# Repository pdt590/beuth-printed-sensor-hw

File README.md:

# PrintED

Readout device hardware for PrintED project

- Readout Device

Front                              |  Edge
:---------------------------------:|:--------------------------------------:
  | 

- Readout Device with PrintED Sensor

- System Deployment

## Compatibility

- [beuth-printed-sensor-fw](https://github.com/pdt590/beuth-printed-sensor-fw)
- [beuth-printed-app](https://github.com/pdt590/beuth-printed-app)
- [beuth-printed-cloud](https://github.com/pdt590/beuth-printed-cloud)

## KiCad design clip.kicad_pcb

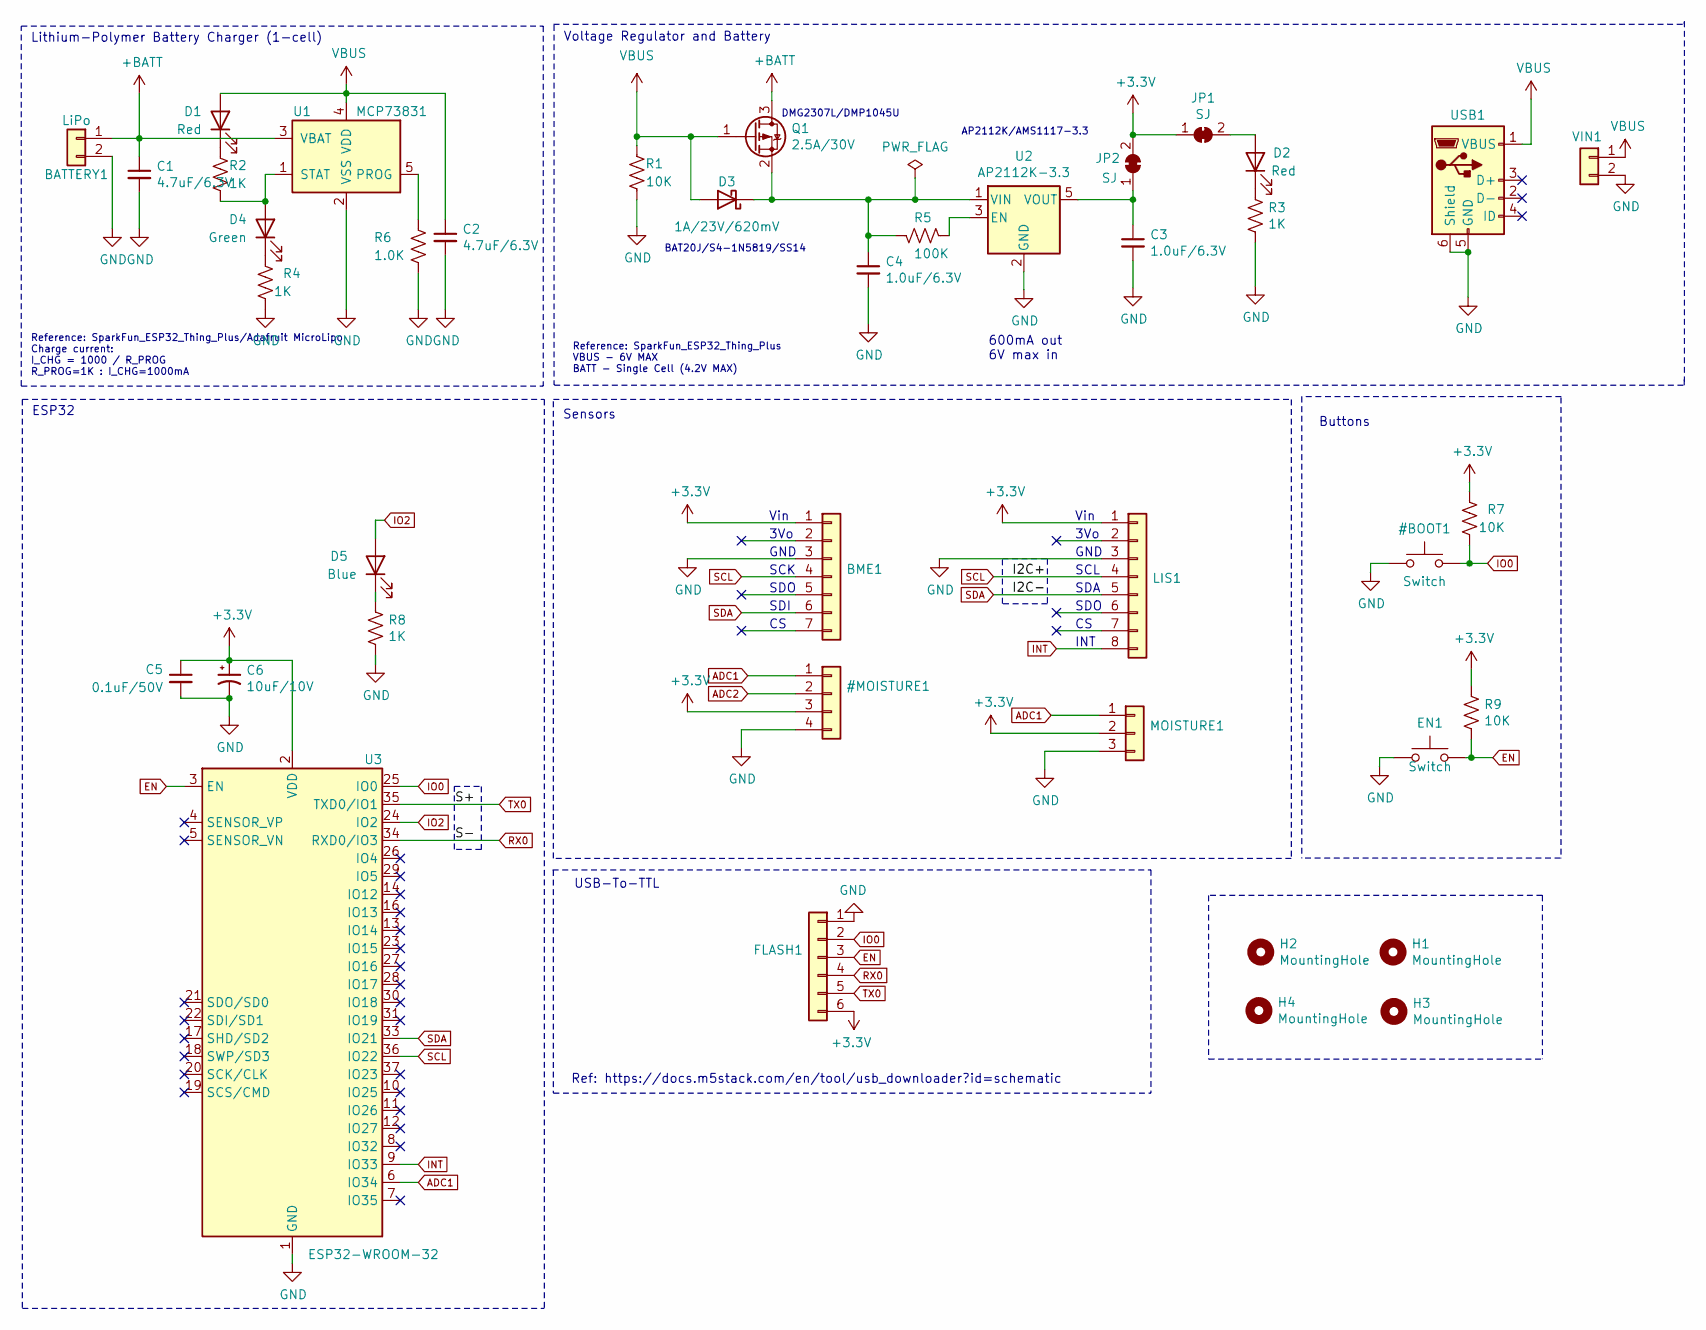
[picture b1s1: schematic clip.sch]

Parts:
BATTERY1: LiPo; JST_PH_S2B-PH-K_1x02_P2.00mm_Horizontal; Digikey 455-1719-ND
BME1: BME680; PinHeader_1x07_P2.54mm_Vertical; Digikey S7006-ND
C1, C2: 4.7uF/6.3V; C_0805_2012Metric_Pad1.15x1.40mm_HandSolder; Digikey 732-7647-1-ND
C3, C4: 1.0uF/6.3V; C_0805_2012Metric_Pad1.15x1.40mm_HandSolder; Digikey 732-7654-1-ND
C5: 0.1uF/50V; C_0805_2012Metric_Pad1.15x1.40mm_HandSolder; Digikey 732-8080-1-ND
C6: 10uF/10V; C_0805_2012Metric_Pad1.15x1.40mm_HandSolder; Digikey 478-3346-1-ND
D1: Red; LED_0805_2012Metric_Pad1.15x1.40mm_HandSolder; Digikey 732-4984-1-ND
D2: Red; LED_0805_2012Metric_Pad1.15x1.40mm_HandSolder; Digikey 732-4987-1-ND
D3: 1A/23V/620mV; D_SOD-323_HandSoldering; Digikey 497-3381-1-ND
D4: Green; LED_0805_2012Metric_Pad1.15x1.40mm_HandSolder; Digikey 732-4983-1-ND
D5: Blue; LED_0805_2012Metric_Pad1.15x1.40mm_HandSolder; Digikey 732-4982-1-ND
EN1: Switch; SW_SPST_B3U-1000P-B; Digikey SW1020CT-ND
FLASH1: Conn_01x07; PinHeader_1x06_P2.54mm_Vertical; Digikey 732-5323-ND
H1, H2, H3, H4: MountingHole; MountingHole_2.2mm_M2_DIN965_Pad
JP1, JP2: SJ; SolderJumper-2_P1.3mm_Open_TrianglePad1.0x1.5mm; Digikey 732-5328-ND
LIS1: LIS3DH; PinHeader_1x08_P2.54mm_Vertical; Digikey S7006-ND
MOISTURE1: MOISTURE; PinHeader_1x03_P2.54mm_Vertical
Q1: 2.5A/30V; SOT-23_Handsoldering; Digikey DMG2307L-7DICT-ND
R1, R7, R9: 10K; R_0805_2012Metric_Pad1.15x1.40mm_HandSolder; Digikey P10KDACT-ND
R2, R3, R4, R8: 1K; R_0805_2012Metric_Pad1.15x1.40mm_HandSolder; Digikey P1.0KDACT-ND
R5: 100K; R_0805_2012Metric_Pad1.15x1.40mm_HandSolder; Digikey P100KDACT-ND
R6: 1.0K; R_0805_2012Metric_Pad1.15x1.40mm_HandSolder; Digikey P2.0KDACT-ND
U1: MCP73831; SOT-23-5_HandSoldering; Digikey MCP73831T-2ACI/OTCT-ND
U2: AP2112K-3.3; SOT-23-5_HandSoldering; Digikey AP2112K-3.3TRG1DICT-ND
U3: ESP32-WROOM-32; Digikey 1904-1010-1-ND
USB1: USB_B_Micro; USB_Micro-B_Wuerth_629105150521; Digikey 732-5960-1-ND
VIN1: Conn_01x07; PinHeader_1x02_P2.54mm_Vertical; Digikey 732-5323-ND

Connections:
+BATT: BATTERY1.1, C1.1, Q1.3 (D), U1.3 (VBAT)
EN: EN1.2, FLASH1.3, R9.2, U3.3 (EN)
INT: LIS1.8, U3.9 (IO33)
IO2: D5.2 (A), U3.24 (IO2)
unnamed: C3.1, JP2.1 (A), U2.5 (VOUT)
unnamed: C4.1, D3.1 (K), Q1.2 (S), R5.2, U2.1 (VIN)
unnamed: D1.1 (K), R2.2
unnamed: D2.1 (K), R3.1
unnamed: D2.2 (A), JP1.2 (B)
unnamed: D4.1 (K), R4.2
unnamed: D4.2 (A), R2.1, U1.1 (STAT)
unnamed: D5.1 (K), R8.1
unnamed: R5.1, U2.3 (EN)
unnamed: R6.1, U1.5 (PROG)
RX0: FLASH1.4, U3.34 (RXD0/IO3)
SCL: BME1.4, LIS1.4, U3.36 (IO22)
SDA: BME1.6, LIS1.5, U3.33 (IO21)
TX0: FLASH1.5, U3.35 (TXD0/IO1)
VBUS: C2.1, D1.2 (A), D3.2 (A), Q1.1 (G), R1.2, U1.4 (VDD), USB1.1 (VBUS), VIN1.1

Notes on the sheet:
Voltage Regulator and Battery
Lithium-Polymer Battery Charger (1-cell)
ESP32
Buttons
Sensors
AP2112K/AMS1117-3.3
DMG2307L/DMP1045U
BAT20J/S4-1N5819/SS14
600mA out 6V max in
INT
SDO
SDA
SCL
GND
3Vo
Vin
SDI
SCK
GND
Reference: SparkFun_ESP32_Thing_Plus/Adafruit MicroLipo Charge current: I_CHG = 1000 / R_PROG R_PROG=1K : I_CHG=1000mA
Reference: SparkFun_ESP32_Thing_Plus VBUS - 6V MAX BATT - Single Cell (4.2V MAX)
Ref: https://docs.m5stack.com/en/tool/usb_downloader?id=schematic
USB-To-TTL

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
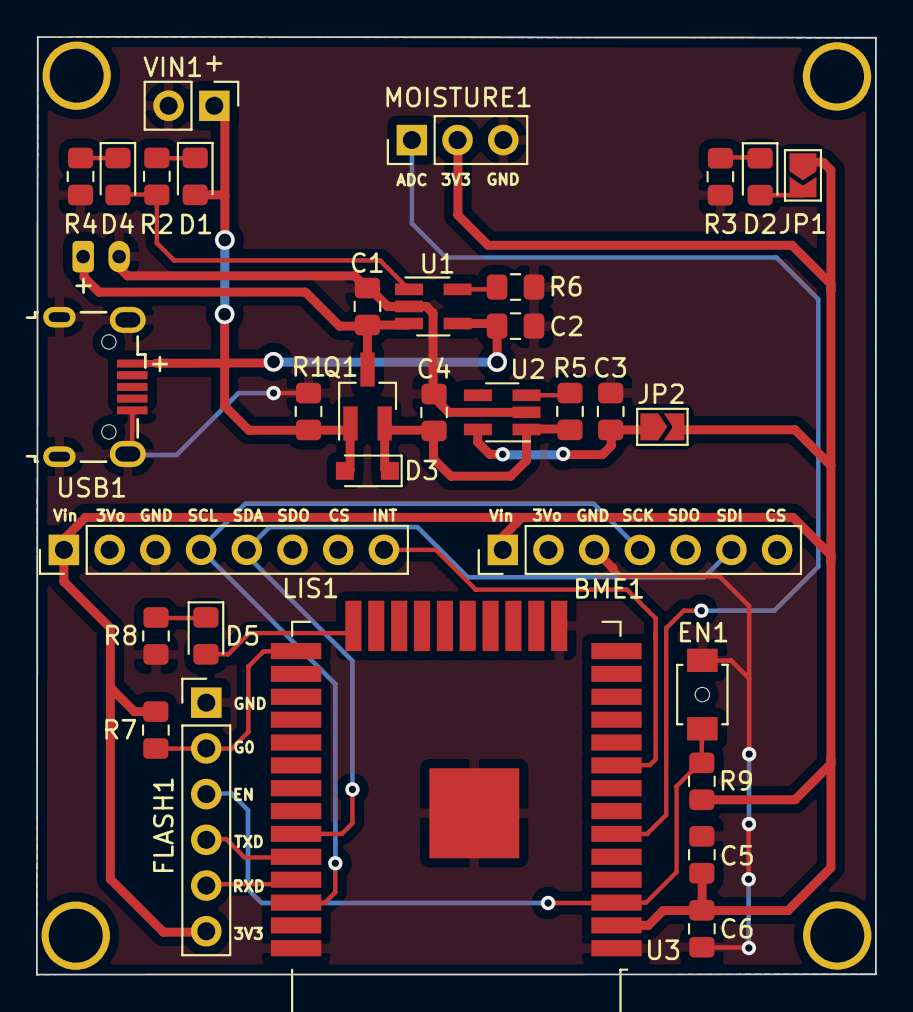
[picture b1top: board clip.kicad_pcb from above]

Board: 2 copper layers, 46.6 x 52.1 mm, 38 parts (1 on the bottom side), 23 nets.

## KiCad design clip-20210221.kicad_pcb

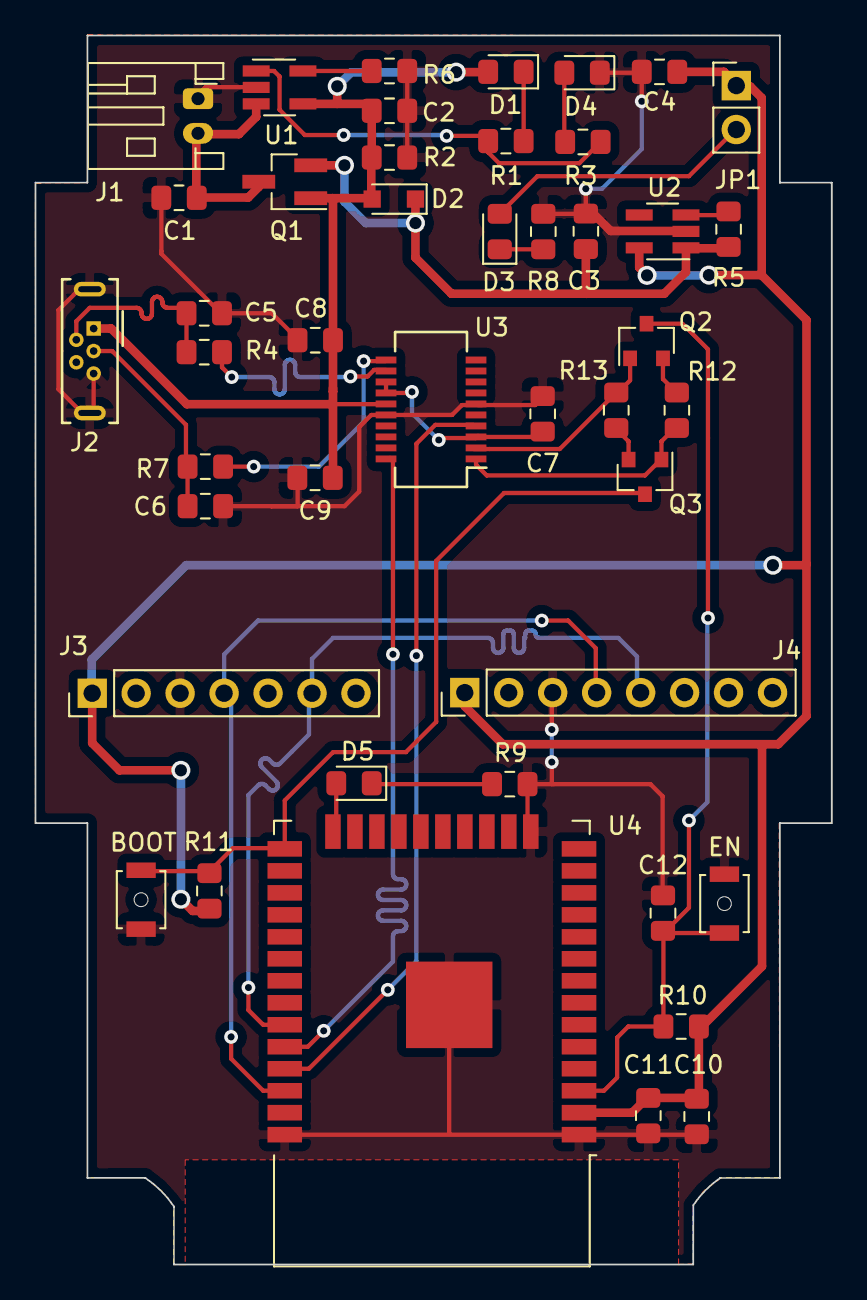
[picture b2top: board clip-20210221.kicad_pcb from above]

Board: 2 copper layers, 46.0 x 71.0 mm, 44 parts (0 on the bottom side), 29 nets.

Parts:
BOOT: Switch; SW_SPST_B3U-1000P-B
C1, C2, C9: 4.7uF/6.3V; C_0805_2012Metric_Pad1.15x1.40mm_HandSolder
C3, C4: 1.0uF/6.3V; C_0805_2012Metric_Pad1.15x1.40mm_HandSolder
C5, C6: 47pF/16V; C_0805_2012Metric_Pad1.15x1.40mm_HandSolder
C7, C8, C10, C12: 0.1uF/50V; C_0805_2012Metric_Pad1.15x1.40mm_HandSolder
C11: 10uF/10V; C_0805_2012Metric_Pad1.15x1.40mm_HandSolder
D1: Red; LED_0805_2012Metric_Pad1.15x1.40mm_HandSolder
D2: 1A/23V/620mV; D_SOD-323_HandSoldering
D3: Yellow; LED_0805_2012Metric_Pad1.15x1.40mm_HandSolder
D4: Green; LED_0805_2012Metric_Pad1.15x1.40mm_HandSolder
D5: Blue; LED_0805_2012Metric_Pad1.15x1.40mm_HandSolder
EN: Switch; SW_SPST_B3U-1000P-B
J1: LiPo; JST_PH_S2B-PH-K_1x02_P2.00mm_Horizontal
J2: USB_B_Micro; USB_Micro-B_Wuerth_614105150721_Vertical
J3: BME680; PinHeader_1x07_P2.54mm_Vertical
J4: LIS3DH; PinHeader_1x08_P2.54mm_Vertical
JP1: SJ; PinHeader_1x02_P2.54mm_Vertical
Q1: 2.5A/30V; SOT-23_Handsoldering
Q2, Q3: S8050; SOT-23
R1, R3, R8, R9: 1K; R_0805_2012Metric_Pad1.15x1.40mm_HandSolder
R2, R10, R11, R12, R13: 10K; R_0805_2012Metric_Pad1.15x1.40mm_HandSolder
R4, R7: 27; R_0805_2012Metric_Pad1.15x1.40mm_HandSolder
R5: 100K; R_0805_2012Metric_Pad1.15x1.40mm_HandSolder
R6: 2.0K; R_0805_2012Metric_Pad1.15x1.40mm_HandSolder
U1: MCP73831; SOT-23-5_HandSoldering
U2: AP2112K-3.3; SOT-23-5_HandSoldering
U3: FT231XS; SSOP-20_3.9x8.7mm_P0.635mm
U4: ESP32-WROOM-32

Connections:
+3V3: C4.1, C10.1, C11.1, J3.1, J4.1, JP1.1, R10.1, R11.2, U2.5, U4.2
+BATT: C1.1, J1.2, Q1.3, U1.3
/D+: C6.1, J2.3, R7.1
/D-: C5.1, J2.2, R4.1
EN: C12.1, EN.2, Q2.3, R10.2, U4.3
GND: BOOT.1, C1.2, C2.2, C3.2, C4.2, C5.2, C6.2, C7.2, C8.2, C9.2, C10.2, C11.2, C12.2, D4.1, EN.1, J1.1, J2.5, J2.6, J3.3, J4.3, R2.1, R6.2, R8.2, R9.2, U1.2, U2.2, U3.6, U3.16, U4.1, U4.15, U4.38, U4.39
IO0: BOOT.2, Q3.3, R11.1, U4.25
IO2: D5.2, U4.24
unnamed: C7.1, U3.3, U3.13, U3.14
unnamed: D1.1, R1.2
unnamed: D3.1, R8.1
unnamed: D3.2, JP1.2
unnamed: D4.2, R3.1
unnamed: D5.1, R9.1
unnamed: Q2.2, R12.2
unnamed: Q3.2, R13.1
unnamed: R1.1, R3.2, U1.1
unnamed: R4.2, U3.12
unnamed: R5.1, U2.3
unnamed: R6.1, U1.5
unnamed: R7.2, U3.11
RX0: U3.20, U4.34
SCL: J3.4, J4.4, U4.36
SDA: J3.6, J4.5, U4.33
TX0: U3.4, U4.35
VBUS: C2.1, C8.1, C9.1, D1.2, D2.2, J2.1, Q1.1, R2.2, U1.4, U3.15
VIN: C3.1, D2.1, Q1.2, R5.2, U2.1
~DTR: Q3.1, R12.1, U3.1
~RTS: Q2.1, R13.2, U3.2

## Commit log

2021-01-21 Rename project
2021-03-02 Update design
2021-03-31 Add Moisture Sensor Header
2021-04-23 Refactor design
2021-06-30 Refactor files
2021-08-26 Bump design
2021-09-21 Fix typo
